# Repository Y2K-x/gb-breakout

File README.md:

# gb-breakout
A Game Boy breakout board for CMOS-level devices

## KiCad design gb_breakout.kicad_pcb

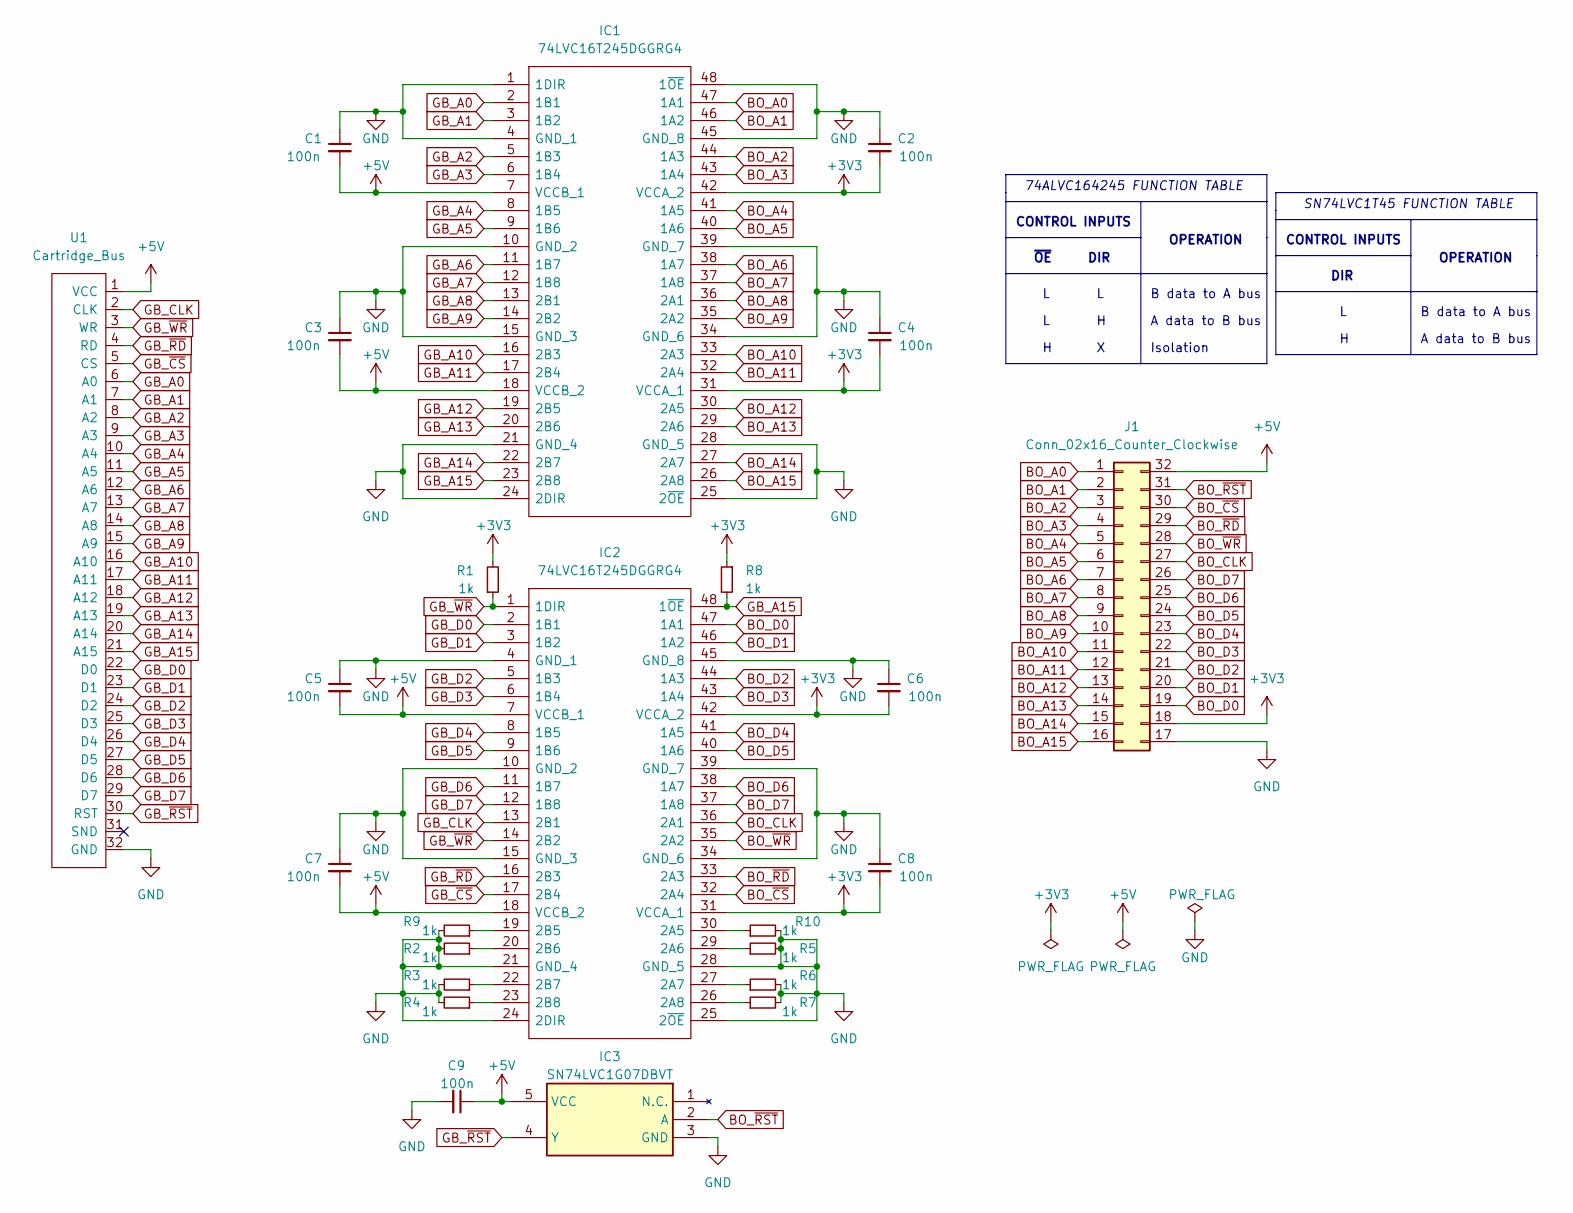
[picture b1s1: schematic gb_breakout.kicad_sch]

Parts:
C1, C2, C3, C4, C5, C6, C7, C8, C9: 100n; C_0603_1608Metric
IC1, IC2: 74LVC16T245DGGRG4; SOP50P810X120-48N; Mouser Part Number 595-4LVC16T245DGGRG4
IC3: SN74LVC1G07DBVT; SOT95P280X145-5N; Mouser Part Number 595-SN74LVC1G07DBVT
J1: Conn_02x16_Counter_Clockwise; PinHeader_2x16_P2.54mm_Vertical_SMD
R1, R2, R3, R4, R5, R6, R7, R8, R9, R10: 1k; R_0402_1005Metric
U1: Cartridge_Bus; GB_Cartridge

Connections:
+3V3: C2.2, C4.2, C6.2, C8.2, IC1.31 (VCCA_1), IC1.42 (VCCA_2), IC2.31 (VCCA_1), IC2.42 (VCCA_2), J1.18, R1.2, R8.1
+5V: C1.2, C3.2, C5.2, C7.2, C9.1, IC1.7 (VCCB_1), IC1.18 (VCCB_2), IC2.7 (VCCB_1), IC2.18 (VCCB_2), IC3.5 (VCC), J1.32, U1.1 (VCC)
BO_A0: IC1.47 (1A1), J1.1
BO_A1: IC1.46 (1A2), J1.2
BO_A2: IC1.44 (1A3), J1.3
BO_A3: IC1.43 (1A4), J1.4
BO_A4: IC1.41 (1A5), J1.5
BO_A5: IC1.40 (1A6), J1.6
BO_A6: IC1.38 (1A7), J1.7
BO_A7: IC1.37 (1A8), J1.8
BO_A8: IC1.36 (2A1), J1.9
BO_A9: IC1.35 (2A2), J1.10
BO_A10: IC1.33 (2A3), J1.11
BO_A11: IC1.32 (2A4), J1.12
BO_A12: IC1.30 (2A5), J1.13
BO_A13: IC1.29 (2A6), J1.14
BO_A14: IC1.27 (2A7), J1.15
BO_A15: IC1.26 (2A8), J1.16
BO_CLK: IC2.36 (2A1), J1.27
BO_D0: IC2.47 (1A1), J1.19
BO_D1: IC2.46 (1A2), J1.20
BO_D2: IC2.44 (1A3), J1.21
BO_D3: IC2.43 (1A4), J1.22
BO_D4: IC2.41 (1A5), J1.23
BO_D5: IC2.40 (1A6), J1.24
BO_D6: IC2.38 (1A7), J1.25
BO_D7: IC2.37 (1A8), J1.26
BO_~CS: IC2.32 (2A4), J1.30
BO_~RD: IC2.33 (2A3), J1.29
BO_~RST: IC3.2 (A), J1.31
BO_~WR: IC2.35 (2A2), J1.28
GB_A0: IC1.2 (1B1), U1.6 (A0)
GB_A1: IC1.3 (1B2), U1.7 (A1)
GB_A2: IC1.5 (1B3), U1.8 (A2)
GB_A3: IC1.6 (1B4), U1.9 (A3)
GB_A4: IC1.8 (1B5), U1.10 (A4)
GB_A5: IC1.9 (1B6), U1.11 (A5)
GB_A6: IC1.11 (1B7), U1.12 (A6)
GB_A7: IC1.12 (1B8), U1.13 (A7)
GB_A8: IC1.13 (2B1), U1.14 (A8)
GB_A9: IC1.14 (2B2), U1.15 (A9)
GB_A10: IC1.16 (2B3), U1.16 (A10)
GB_A11: IC1.17 (2B4), U1.17 (A11)
GB_A12: IC1.19 (2B5), U1.18 (A12)
GB_A13: IC1.20 (2B6), U1.19 (A13)
GB_A14: IC1.22 (2B7), U1.20 (A14)
GB_A15: IC1.23 (2B8), IC2.48 (1~OE), R8.2, U1.21 (A15)
GB_CLK: IC2.13 (2B1), U1.2 (CLK~)
GB_D0: IC2.2 (1B1), U1.22 (D0)
GB_D1: IC2.3 (1B2), U1.23 (D1)
GB_D2: IC2.5 (1B3), U1.24 (D2)
GB_D3: IC2.6 (1B4), U1.25 (D3)
GB_D4: IC2.8 (1B5), U1.26 (D4)
GB_D5: IC2.9 (1B6), U1.27 (D5)
GB_D6: IC2.11 (1B7), U1.28 (D6)
GB_D7: IC2.12 (1B8), U1.29 (D7)
GB_~CS: IC2.17 (2B4), U1.5 (CS)
GB_~RD: IC2.16 (2B3), U1.4 (RD)
GB_~RST: IC3.4 (Y), U1.30 (RST)
GB_~WR: IC2.1 (1DIR), IC2.14 (2B2), R1.1, U1.3 (WR)
GND: C1.1, C2.1, C3.1, C4.1, C5.1, C6.1, C7.1, C8.1, C9.2, IC1.1 (1DIR), IC1.4 (GND_1), IC1.10 (GND_2), IC1.15 (GND_3), IC1.21 (GND_4), IC1.24 (2DIR), IC1.25 (2~OE), IC1.28 (GND_5), IC1.34 (GND_6), IC1.39 (GND_7), IC1.45 (GND_8), IC1.48 (1~OE), IC2.4 (GND_1), IC2.10 (GND_2), IC2.15 (GND_3), IC2.21 (GND_4), IC2.24 (2DIR), IC2.25 (2~OE), IC2.28 (GND_5), IC2.34 (GND_6), IC2.39 (GND_7), IC2.45 (GND_8), IC3.3 (GND), J1.17, R2.2, R3.2, R4.2, R5.2, R6.2, R7.2, R9.2, R10.2, U1.32 (GND)
unnamed: IC2.30 (2A5), R10.1
unnamed: IC2.29 (2A6), R5.1
unnamed: IC2.27 (2A7), R6.1
unnamed: IC2.26 (2A8), R7.1
unnamed: IC2.19 (2B5), R9.1
unnamed: IC2.20 (2B6), R2.1
unnamed: IC2.22 (2B7), R3.1
unnamed: IC2.23 (2B8), R4.1

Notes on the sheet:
DIR
B data to A bus
CONTROL INPUTS
OPERATION
Isolation
A data to B bus
74ALVC164245 FUNCTION TABLE
SN74LVC1T45 FUNCTION TABLE
~{OE}

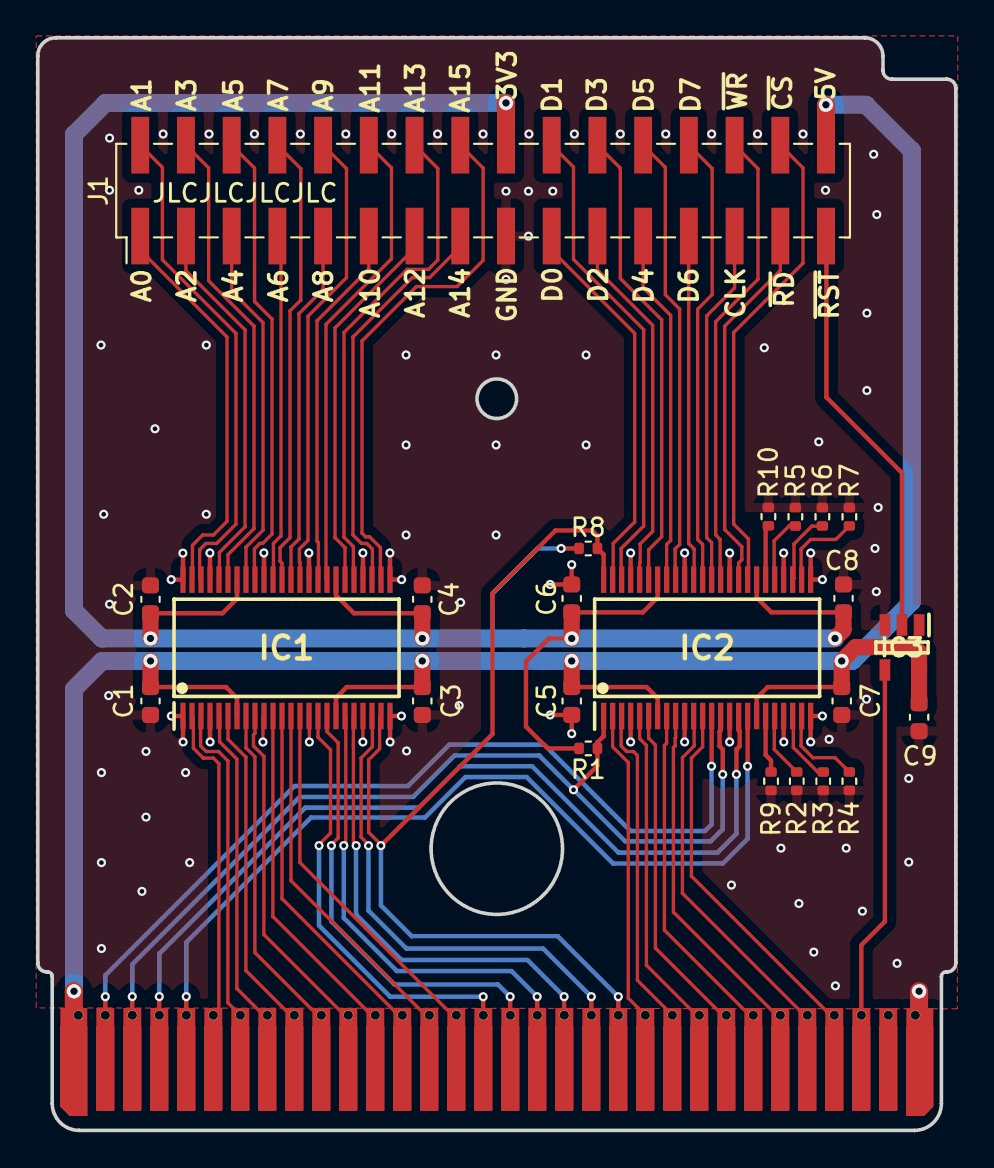
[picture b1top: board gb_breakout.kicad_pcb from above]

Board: 2 copper layers, 51.0 x 60.7 mm, 24 parts (0 on the bottom side), 69 nets.

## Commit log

2022-12-20 add initial files + submodules
2022-12-20 add libs + fix associations
2022-12-20 finished power+gnd routing
2022-12-20 removed floating traces that were hidden under other traces + vias
2022-12-20 begin routing address lines
2022-12-20 switched to 74ALVC164245 for level shifting
2022-12-20 update gb kicad lib to latest commit
2022-12-20 finish routing address lines, start routing data lines
2022-12-20 add bus transciever 3d model
2022-12-20 switch decoupling caps to imperial 0603
2022-12-21 add oshw logo for silkscreeen
2022-12-21 finish cart edge routing to bus transcievers
2022-12-21 fix pin header pinout to make better sense to route
2022-12-21 PCB done
2022-12-21 update gitignore to ignore gerbers
2022-12-21 change 0201 resistor to 0402, woops
2022-12-21 add BOM
2022-12-21 add renders and update README
2022-12-21 fix mistake in README
2022-12-21 im dumb
2022-12-21 add pulldown resistors to floating transciever pins, update render, update BOM
2022-12-28 replace bus transciever with SN74LVC16T245 to remove power sequencing requirement
2022-12-28 update BOM
2022-12-28 OE on 2nd bus transciever now connected to A15, isolates data bus from the cartridge when GB is not accessing the cartridge specifically (ROM reads only at the moment)
2022-12-28 update render images
2022-12-29 update BOM with digikey links instead, cheaper BOM price
2023-05-11 add SN74LVC1T45DBVT library
2023-05-11 fixed reset line direction in schematic by adding a dedicated bus transciever
2023-05-11 disconnect reset signal from IC2
2023-05-16 remove SN74LVC1T45 library & references since it's not what I need
2023-05-16 add SN74LVC1G07 open drain buffer
2023-05-16 add open drain buffer to reset line
2023-05-16 route open drain buffer on PCB
